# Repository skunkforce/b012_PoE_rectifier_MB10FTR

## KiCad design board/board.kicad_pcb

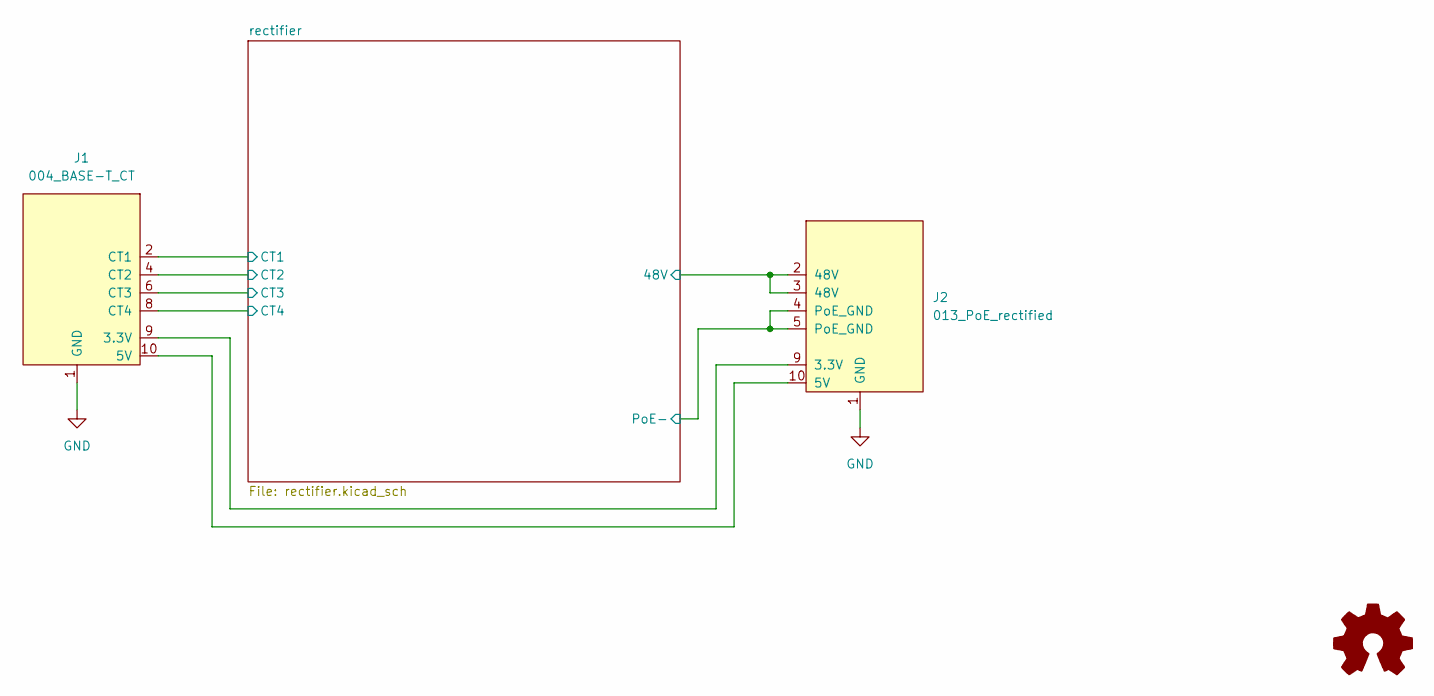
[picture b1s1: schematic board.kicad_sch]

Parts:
J1: 004_BASE-T_CT; on_edge_2x05_device
J2: 013_PoE_rectified; on_edge_2x05_host
LOGO1: Logo_Open_Hardware_Small; OSHW-Symbol_6.7x6mm_SilkScreen

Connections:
/rectifier/48V: J2.2 (48V), J2.3 (48V); also elsewhere on the board
/rectifier/CT1: J1.2 (CT1); also elsewhere on the board
/rectifier/CT2: J1.4 (CT2); also elsewhere on the board
/rectifier/CT3: J1.6 (CT3); also elsewhere on the board
/rectifier/CT4: J1.8 (CT4); also elsewhere on the board
/rectifier/PoE-: J2.4 (PoE_GND), J2.5 (PoE_GND); also elsewhere on the board
GND: J1.1 (GND), J2.1 (GND)
unnamed: J1.10 (5V), J2.10 (5V)
unnamed: J1.9 (3.3V), J2.9 (3.3V)

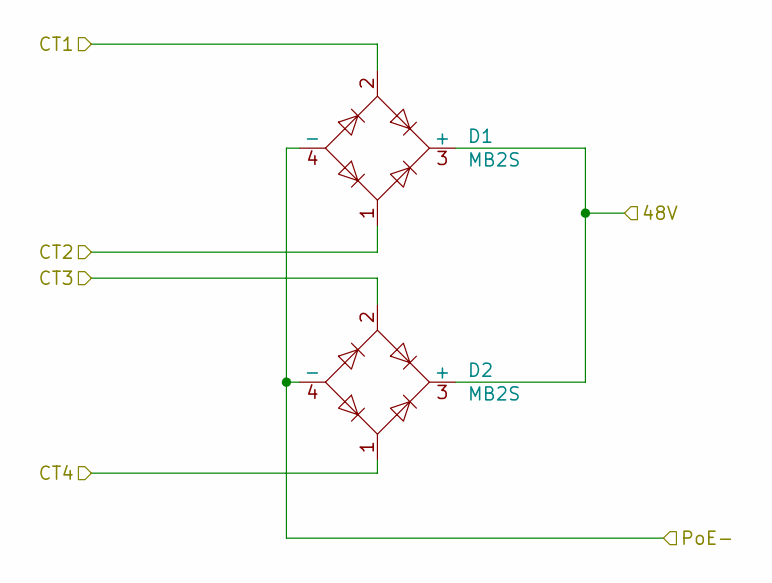
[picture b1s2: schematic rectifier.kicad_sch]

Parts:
D1, D2: MB2S; TO-269AA

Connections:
/rectifier/48V: D1.3 (+), D2.3 (+); also elsewhere on the board
/rectifier/CT1: D1.2; also elsewhere on the board
/rectifier/CT2: D1.1; also elsewhere on the board
/rectifier/CT3: D2.2; also elsewhere on the board
/rectifier/CT4: D2.1; also elsewhere on the board
/rectifier/PoE-: D1.4 (-), D2.4 (-); also elsewhere on the board

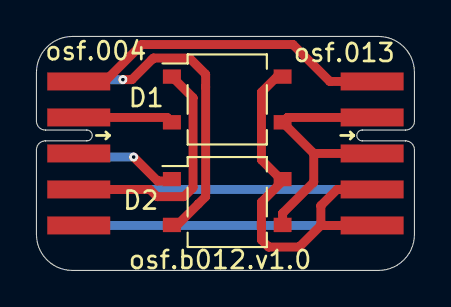
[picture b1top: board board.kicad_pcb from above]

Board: 2 copper layers, 21.0 x 13.0 mm, 5 parts (1 on the bottom side), 9 nets.

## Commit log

2023-02-27 initial
2023-03-04 updated to v1.0 of put_on_edge
2024-02-16 updated kicad version
